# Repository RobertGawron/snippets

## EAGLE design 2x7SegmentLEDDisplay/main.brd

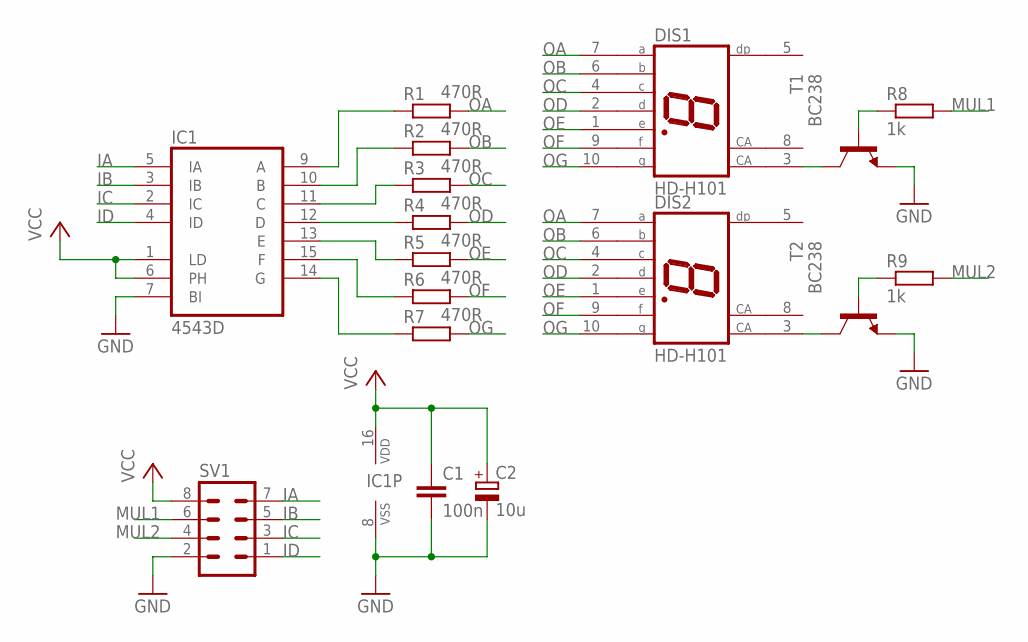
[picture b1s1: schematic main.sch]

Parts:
C1: 100n; C1206
C2: 10u; SMC_A
DIS1, DIS2: HD-H101; HDSP-M
IC1: 4543D; SO16
R1, R2, R3, R4, R5, R6, R7: 470R; R1206
R8, R9: 1k; R1206
SV1: MA04-2
T1, T2: BC238; TO92

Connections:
GND: C1.2, C2.-, IC1.7 (BI), IC1.8 (VSS), SV1.2, T1.1 (E), T2.1 (E)
IA: IC1.5 (IA), SV1.7
IB: IC1.3 (IB), SV1.5
IC: IC1.2 (IC), SV1.3
ID: IC1.4 (ID), SV1.1
MUL1: R8.2, SV1.6
MUL2: R9.2, SV1.4
unnamed: IC1.12 (D), R4.1
unnamed: IC1.11 (C), R3.1
unnamed: IC1.10 (B), R2.1
unnamed: IC1.13 (E), R5.1
unnamed: DIS1.3 (CA), T1.3 (C)
unnamed: R8.1, T1.2 (B)
unnamed: IC1.15 (F), R6.1
unnamed: IC1.9 (A), R1.1
unnamed: IC1.14 (G), R7.1
unnamed: R9.1, T2.2 (B)
unnamed: DIS2.3 (CA), T2.3 (C)
OA: DIS1.7 (A), DIS2.7 (A), R1.2
OB: DIS1.6 (B), DIS2.6 (B), R2.2
OC: DIS1.4 (C), DIS2.4 (C), R3.2
OD: DIS1.2 (D), DIS2.2 (D), R4.2
OE: DIS1.1 (E), DIS2.1 (E), R5.2
OF: DIS1.9 (F), DIS2.9 (F), R6.2
OG: DIS1.10 (G), DIS2.10 (G), R7.2
VCC: C1.1, C2.+, IC1.1 (LD), IC1.6 (PH), IC1.16 (VDD), SV1.8

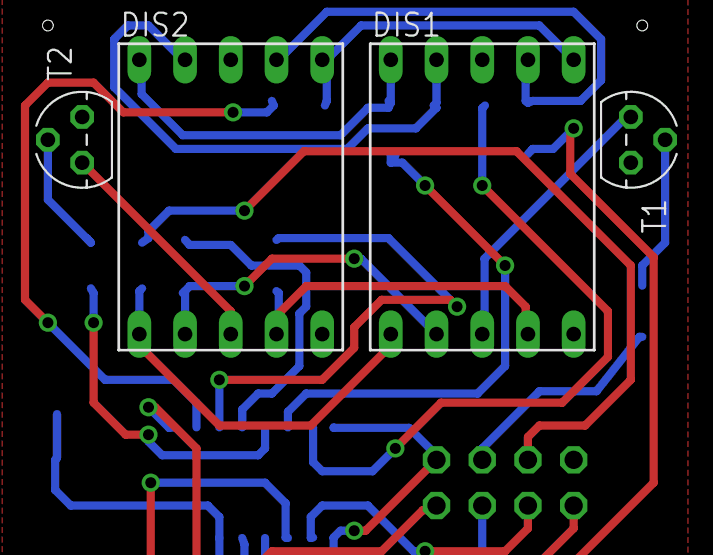
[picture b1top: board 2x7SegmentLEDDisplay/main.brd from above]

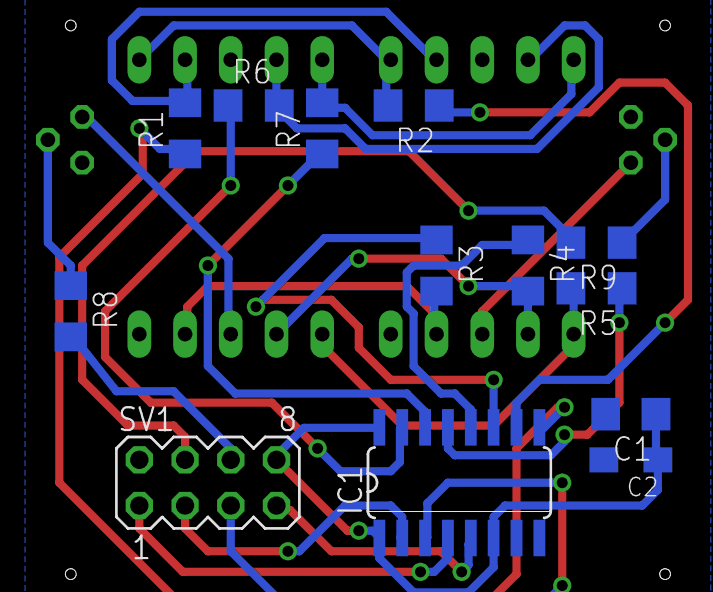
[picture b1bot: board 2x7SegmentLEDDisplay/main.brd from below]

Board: 2 copper layers, 17 parts (13 on the bottom side), 26 nets.

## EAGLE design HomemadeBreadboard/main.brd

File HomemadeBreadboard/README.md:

# Homemade breadboard.

For more info please visit full article:
http://robertgawron.blogspot.com/2015/07/homemade-breadboard.html

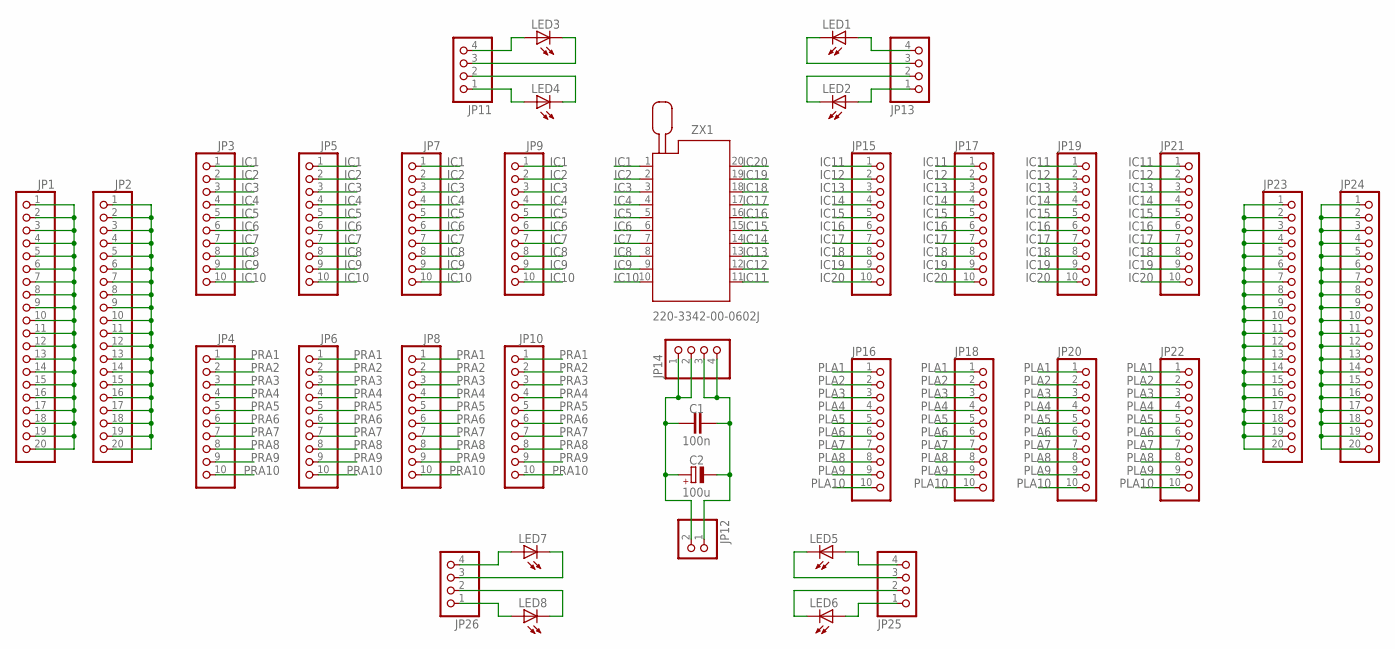
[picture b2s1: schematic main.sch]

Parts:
C1: 100n; C1206
C2: 100u; SMC_A
JP1, JP2, JP23, JP24: PINHD-1X20; 1X20
JP3, JP4, JP5, JP6, JP7, JP8, JP9, JP10, JP15, JP16, JP17, JP18, JP19, JP20, JP21, JP22: PINHD-1X10; 1X10
JP11, JP13, JP14, JP25, JP26: PINHD-1X4; 1X04
JP12: PINHD-1X2/90; 1X02/90
LED1, LED2, LED3, LED4, LED5, LED6, LED7, LED8: LEDSFH482; SFH482
ZX1: 220-3342-00-0602J

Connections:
GND: C1.2, C2.-, JP12.1, JP14.3, JP14.4
IC1: JP3.1, JP5.1, JP7.1, JP9.1, ZX1.1
IC2: JP3.2, JP5.2, JP7.2, JP9.2, ZX1.2
IC3: JP3.3, JP5.3, JP7.3, JP9.3, ZX1.3
IC4: JP3.4, JP5.4, JP7.4, JP9.4, ZX1.4
IC5: JP3.5, JP5.5, JP7.5, JP9.5, ZX1.5
IC6: JP3.6, JP5.6, JP7.6, JP9.6, ZX1.6
IC7: JP3.7, JP5.7, JP7.7, JP9.7, ZX1.7
IC8: JP3.8, JP5.8, JP7.8, JP9.8, ZX1.8
IC9: JP3.9, JP5.9, JP7.9, JP9.9, ZX1.9
IC10: JP3.10, JP5.10, JP7.10, JP9.10, ZX1.10
IC11: JP15.1, JP17.1, JP19.1, JP21.1, ZX1.11
IC12: JP15.2, JP17.2, JP19.2, JP21.2, ZX1.12
IC13: JP15.3, JP17.3, JP19.3, JP21.3, ZX1.13
IC14: JP15.4, JP17.4, JP19.4, JP21.4, ZX1.14
IC15: JP15.5, JP17.5, JP19.5, JP21.5, ZX1.15
IC16: JP15.6, JP17.6, JP19.6, JP21.6, ZX1.16
IC17: JP15.7, JP17.7, JP19.7, JP21.7, ZX1.17
IC18: JP15.8, JP17.8, JP19.8, JP21.8, ZX1.18
IC19: JP15.9, JP17.9, JP19.9, JP21.9, ZX1.19
IC20: JP15.10, JP17.10, JP19.10, JP21.10, ZX1.20
unnamed: JP1.1, JP1.2, JP1.3, JP1.4, JP1.5, JP1.6, JP1.7, JP1.8, JP1.9, JP1.10, JP1.11, JP1.12, JP1.13, JP1.14, JP1.15, JP1.16, JP1.17, JP1.18, JP1.19, JP1.20
unnamed: JP2.1, JP2.2, JP2.3, JP2.4, JP2.5, JP2.6, JP2.7, JP2.8, JP2.9, JP2.10, JP2.11, JP2.12, JP2.13, JP2.14, JP2.15, JP2.16, JP2.17, JP2.18, JP2.19, JP2.20
unnamed: JP24.1, JP24.2, JP24.3, JP24.4, JP24.5, JP24.6, JP24.7, JP24.8, JP24.9, JP24.10, JP24.11, JP24.12, JP24.13, JP24.14, JP24.15, JP24.16, JP24.17, JP24.18, JP24.19, JP24.20
unnamed: JP23.1, JP23.2, JP23.3, JP23.4, JP23.5, JP23.6, JP23.7, JP23.8, JP23.9, JP23.10, JP23.11, JP23.12, JP23.13, JP23.14, JP23.15, JP23.16, JP23.17, JP23.18, JP23.19, JP23.20
unnamed: JP13.3, LED1.K (C)
unnamed: JP13.4, LED1.A
unnamed: JP13.2, LED2.K (C)
unnamed: JP13.1, LED2.A
unnamed: JP11.3, LED3.K (C)
unnamed: JP11.4, LED3.A
unnamed: JP11.2, LED4.K (C)
unnamed: JP11.1, LED4.A
unnamed: JP25.3, LED5.K (C)
unnamed: JP25.4, LED5.A
unnamed: JP25.2, LED6.K (C)
unnamed: JP25.1, LED6.A
unnamed: JP26.3, LED7.K (C)
unnamed: JP26.4, LED7.A
unnamed: JP26.2, LED8.K (C)
unnamed: JP26.1, LED8.A
PLA1: JP16.1, JP18.1, JP20.1, JP22.1
PLA2: JP16.2, JP18.2, JP20.2, JP22.2
PLA3: JP16.3, JP18.3, JP20.3, JP22.3
PLA4: JP16.4, JP18.4, JP20.4, JP22.4
PLA5: JP16.5, JP18.5, JP20.5, JP22.5
PLA6: JP16.6, JP18.6, JP20.6, JP22.6
PLA7: JP16.7, JP18.7, JP20.7, JP22.7
PLA8: JP16.8, JP18.8, JP20.8, JP22.8
PLA9: JP16.9, JP18.9, JP20.9, JP22.9
PLA10: JP16.10, JP18.10, JP20.10, JP22.10
PRA1: JP4.1, JP6.1, JP8.1, JP10.1
PRA2: JP4.2, JP6.2, JP8.2, JP10.2
PRA3: JP4.3, JP6.3, JP8.3, JP10.3
PRA4: JP4.4, JP6.4, JP8.4, JP10.4
PRA5: JP4.5, JP6.5, JP8.5, JP10.5
PRA6: JP4.6, JP6.6, JP8.6, JP10.6
PRA7: JP4.7, JP6.7, JP8.7, JP10.7
PRA8: JP4.8, JP6.8, JP8.8, JP10.8
PRA9: JP4.9, JP6.9, JP8.9, JP10.9
PRA10: JP4.10, JP6.10, JP8.10, JP10.10
VCC: C1.1, C2.+, JP12.2, JP14.1, JP14.2

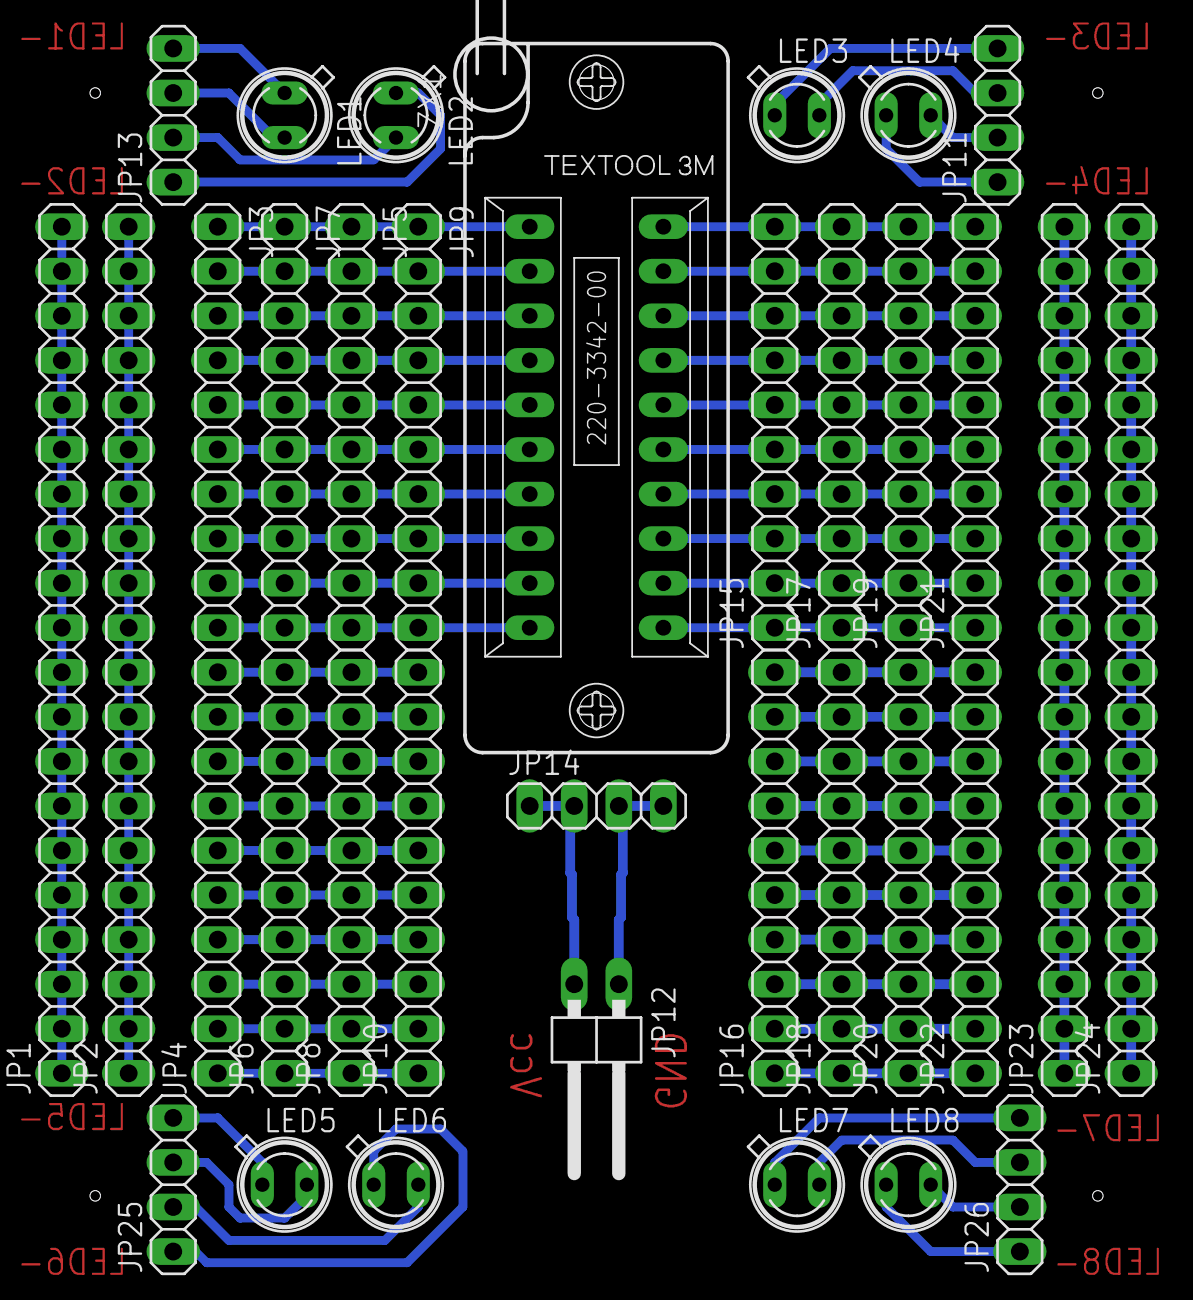
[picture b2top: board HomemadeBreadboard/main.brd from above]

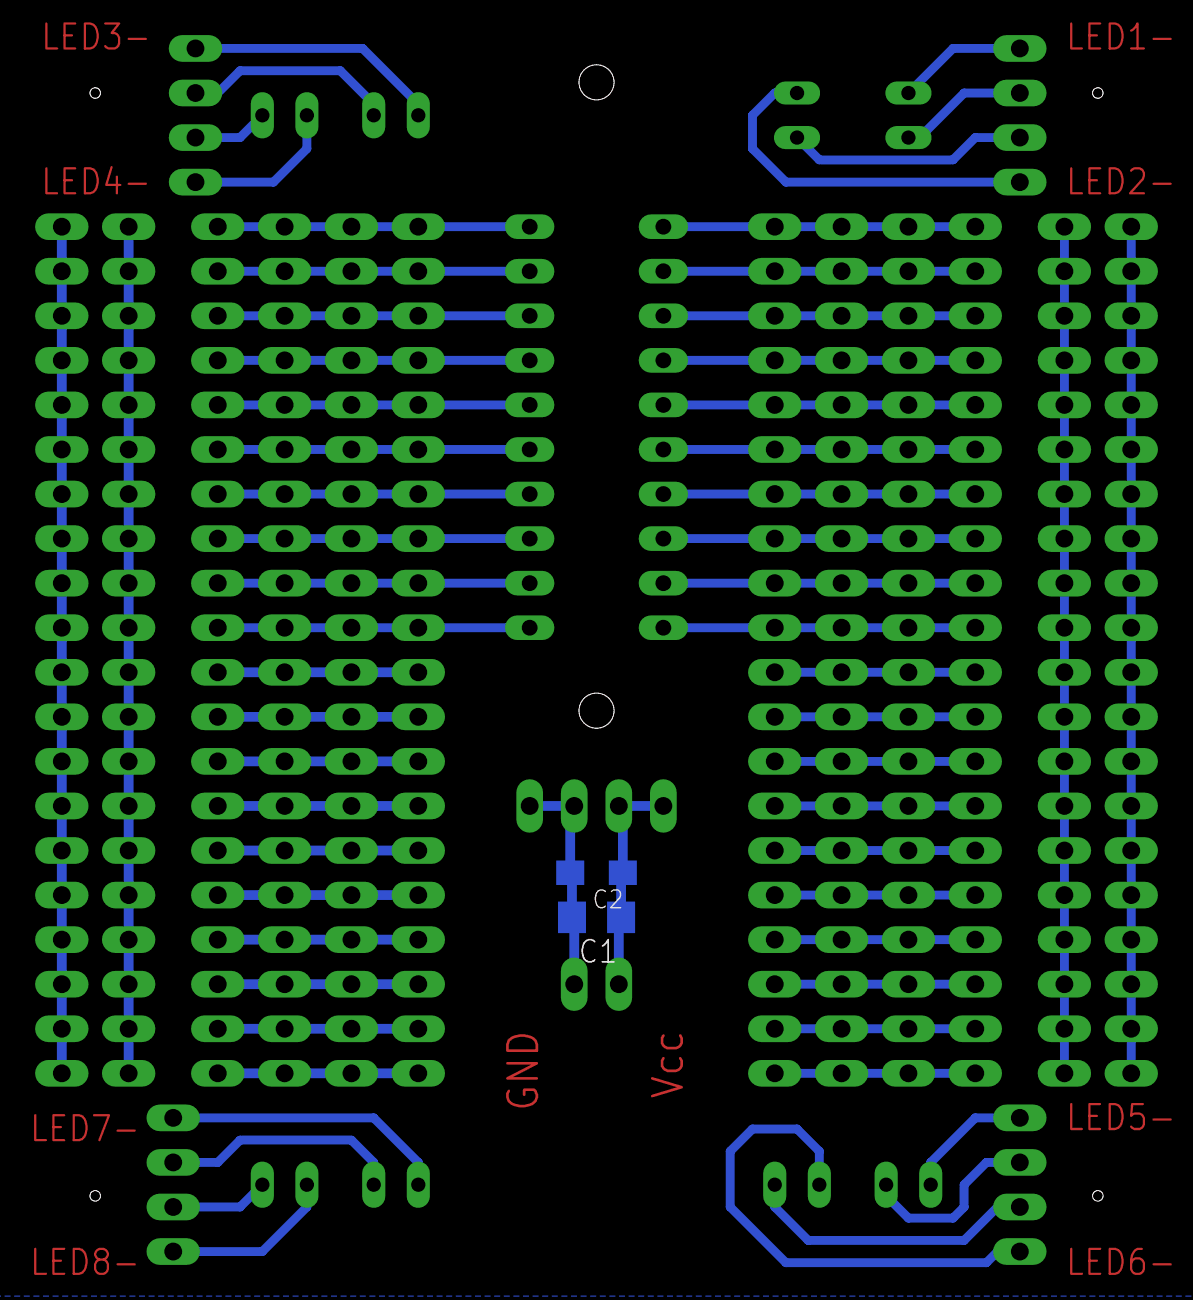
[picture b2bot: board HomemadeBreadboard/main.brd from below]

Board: 2 copper layers, 37 parts (2 on the bottom side), 62 nets.

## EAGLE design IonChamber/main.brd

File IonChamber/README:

This project is not working. It's unfinished.

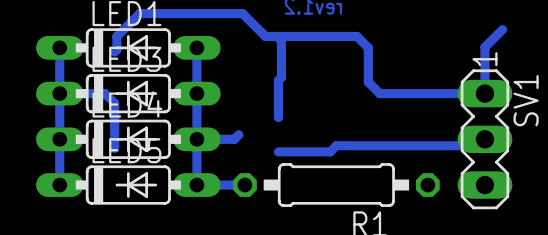
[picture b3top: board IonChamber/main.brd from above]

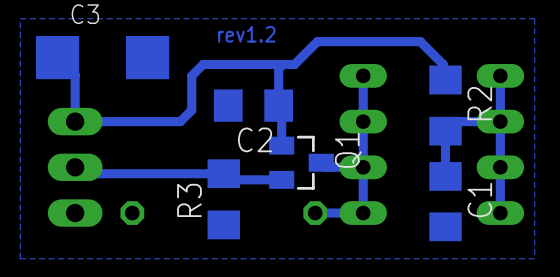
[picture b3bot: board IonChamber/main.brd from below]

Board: 2 copper layers, 12 parts (6 on the bottom side), 5 nets.

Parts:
C1, C2: 100n; C1206
C3: 100u; SMC_C
LED1, LED3, LED4, LED5: 1N4148; DO35-7
Q1: J111; SOT23
R1: 10M; 0207/10
R2: 1k; R1206
R3: 100k; R1206
SV1: connector; MA03-1

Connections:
GND: C1.2, C2.2, C3.-, R1.1, R3.1, SV1.3
unnamed: C1.1, LED1.C, LED3.C, LED4.C, LED5.C, R2.2
unnamed: Q1.2, R3.2, SV1.2
unnamed: LED1.A, LED3.A, LED4.A, LED5.A, Q1.3, R1.2
unnamed: C2.1, C3.+, Q1.1, R2.1, SV1.1

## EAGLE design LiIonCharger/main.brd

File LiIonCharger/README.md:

# USB powered Li-Ion charger.

Be careful, incorrectly connected or overcharged Li-Ion battery can explode or burn. Always load them when you are around.

For more info please visit full article:
http://robertgawron.blogspot.com/2015/07/how-to-make-usb-li-ion-charger.html

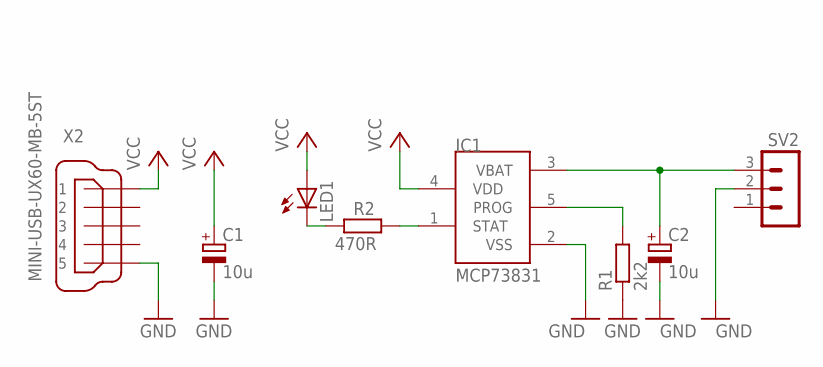
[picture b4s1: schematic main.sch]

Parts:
C1, C2: 10u; SMC_A
IC1: MCP73831; SOT23-5L
LED1: LEDSML0805; SML0805
R1: 2k2; R1206
R2: 470R; R1206
SV2: MA03-1
X2: MINI-USB-UX60-MB-5ST; UX60-MB-5ST

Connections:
GND: C1.-, C2.-, IC1.2 (VSS), R1.1, SV2.2, X2.5
unnamed: IC1.5 (PROG), R1.2
unnamed: LED1.C, R2.1
unnamed: IC1.1 (STAT), R2.2
unnamed: C2.+, IC1.3 (VBAT), SV2.3
VCC: C1.+, IC1.4 (VDD), LED1.A, X2.1

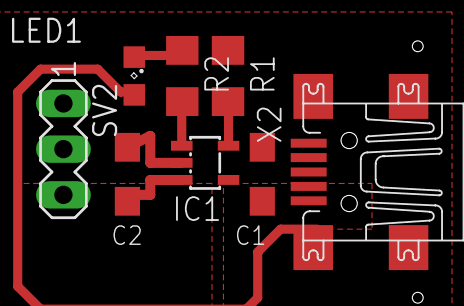
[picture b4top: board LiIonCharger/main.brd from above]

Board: 2 copper layers, 8 parts (0 on the bottom side), 6 nets.

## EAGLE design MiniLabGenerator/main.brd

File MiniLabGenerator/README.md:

# Square wave generator.

For more info please visit full article:
http://robertgawron.blogspot.com/2015/06/poor-mans-lab-generator.html

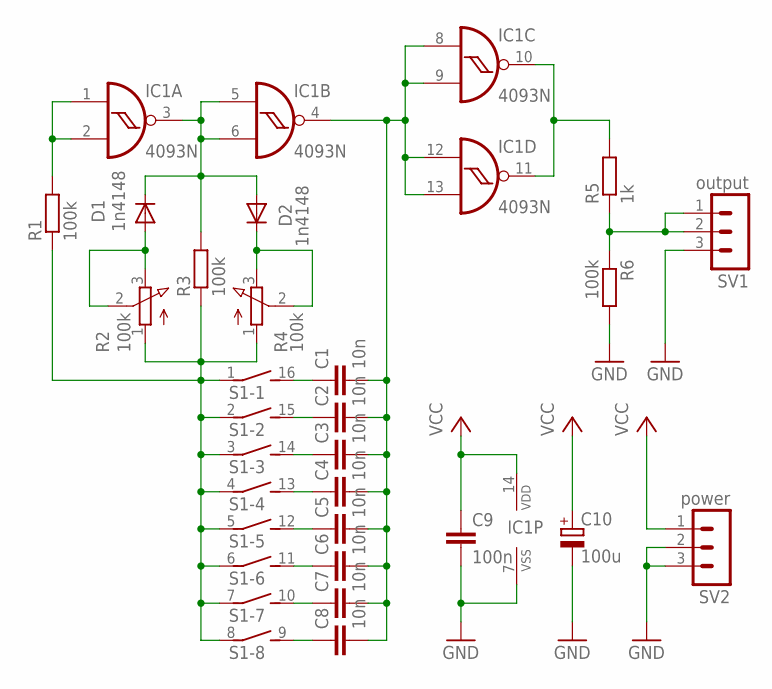
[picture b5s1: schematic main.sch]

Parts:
C1, C2, C3, C4, C5, C6, C7, C8: 10n; C050-025X075
C9: 100n; C1206
C10: 100u; E2,5-7
D1, D2: 1n4148; MINIMELF
IC1: 4093N; DIL14
R1, R3, R6: 100k; 0204V
R2, R4: 100k; 3RP/1610N
R5: 1k; 0204V
S1: DIP08S
SV1: output; MA03-1
SV2: power; MA03-1

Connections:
GND: C9.2, C10.-, IC1.7 (VSS), R6.2, SV1.3, SV2.2, SV2.3
unnamed: D1.C, D2.A, IC1.3 (O), IC1.5 (I0), IC1.6 (I1), R3.2
unnamed: IC1.1 (I0), IC1.2 (I1), R1.2
unnamed: D1.A, R2.2 (S), R2.3 (E)
unnamed: C1.1, S1.16 (2)
unnamed: IC1.10 (O), IC1.11 (O), R5.2
unnamed: R5.1, R6.1, SV1.1, SV1.2
unnamed: C2.1, S1.15 (2)
unnamed: C3.1, S1.14 (2)
unnamed: C4.1, S1.13 (2)
unnamed: C5.1, S1.12 (2)
unnamed: C6.1, S1.11 (2)
unnamed: C7.1, S1.10 (2)
unnamed: C8.1, S1.9 (2)
unnamed: C1.2, C2.2, C3.2, C4.2, C5.2, C6.2, C7.2, C8.2, IC1.4 (O), IC1.8 (I0), IC1.9 (I1), IC1.12 (I0), IC1.13 (I1)
unnamed: D2.C, R4.2 (S), R4.3 (E)
unnamed: R1.1, R2.1 (A), R3.1, R4.1 (A), S1.1, S1.2 (1), S1.3 (1), S1.4 (1), S1.5 (1), S1.6 (1), S1.7 (1), S1.8 (1)
VCC: C9.1, C10.+, IC1.14 (VDD), SV2.1

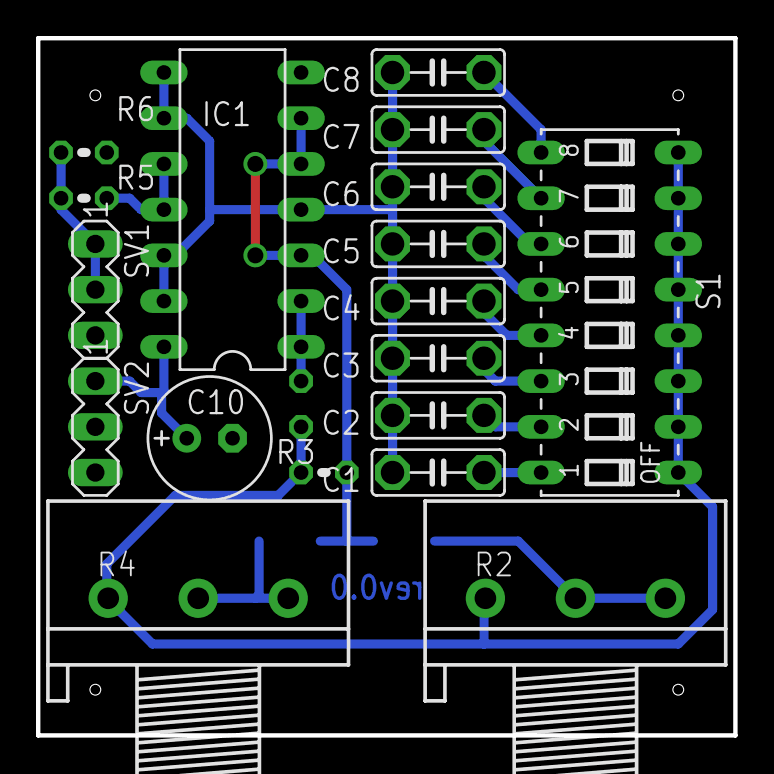
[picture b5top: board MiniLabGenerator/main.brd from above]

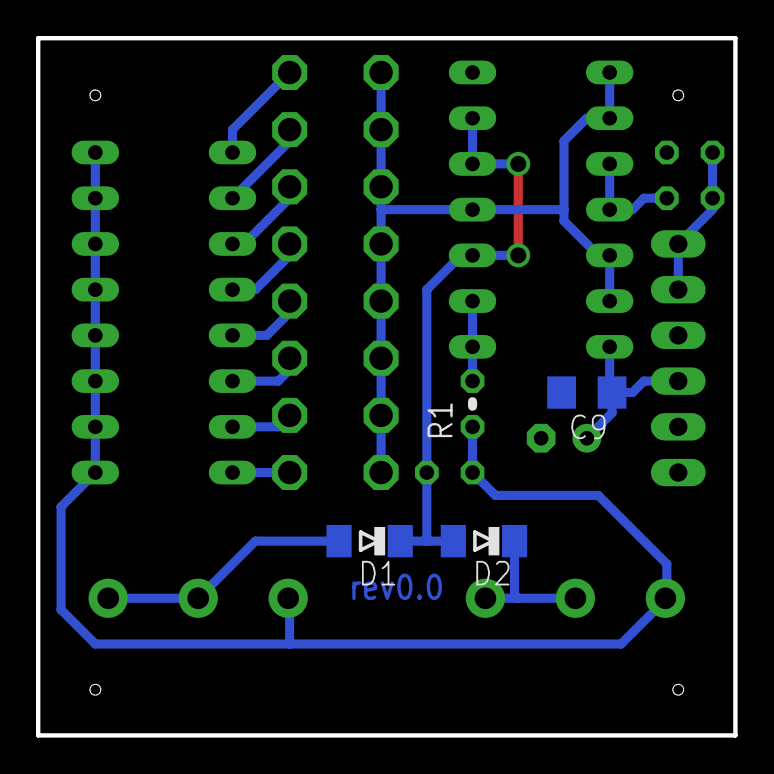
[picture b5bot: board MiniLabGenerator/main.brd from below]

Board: 2 copper layers, 38.7 x 38.7 mm, 22 parts (4 on the bottom side), 18 nets.

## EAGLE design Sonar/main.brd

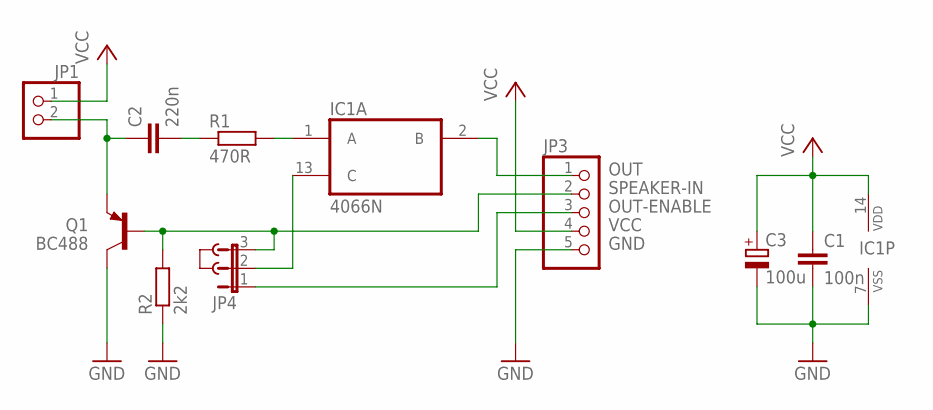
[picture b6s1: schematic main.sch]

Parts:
C1: 100n; C1206
C2: 220n; C025-025X050
C3: 100u; E2-5
IC1: 4066N; DIL14
J1: JUMPER; JUMP
JP1: PINHD-1X2; 1X02
JP3: PINHD-1X5; 1X05
JP4: JP2E; JP2
Q1: BC488; TO92-EBC
R1: 470R; 0204/7
R2: 2k2; R1206

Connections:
GND: C1.2, C3.-, IC1.7 (VSS), JP3.5, Q1.C, R2.1
unnamed: C2.1, JP1.2, Q1.E
unnamed: C2.2, R1.1
unnamed: IC1.1 (A), R1.2
unnamed: IC1.13 (C), JP4.2
OUT: IC1.2 (B), JP3.1
OUT-ENABLE: JP3.3, JP4.1
SPEAKER-IN: JP3.2, JP4.3, Q1.B, R2.2
VCC: C1.1, C3.+, IC1.14 (VDD), JP1.1, JP3.4

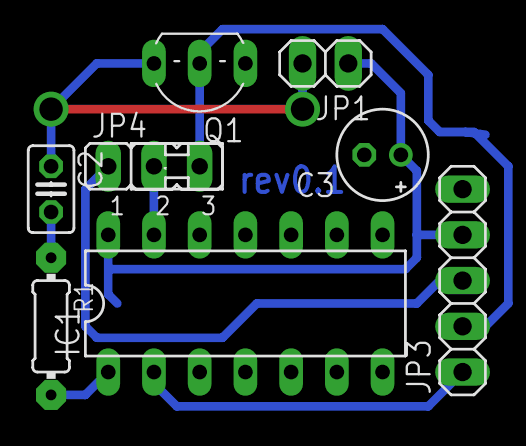
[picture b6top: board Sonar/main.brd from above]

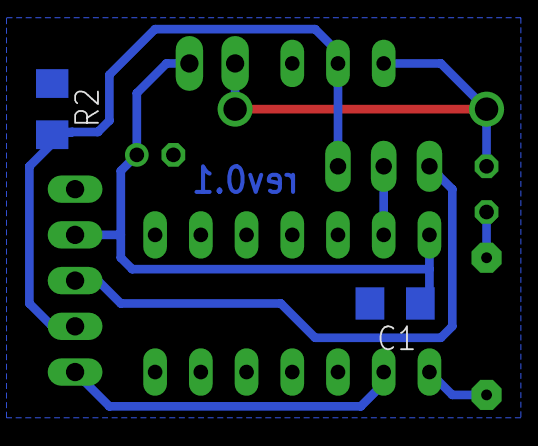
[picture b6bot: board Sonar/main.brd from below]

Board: 2 copper layers, 11 parts (2 on the bottom side), 9 nets.

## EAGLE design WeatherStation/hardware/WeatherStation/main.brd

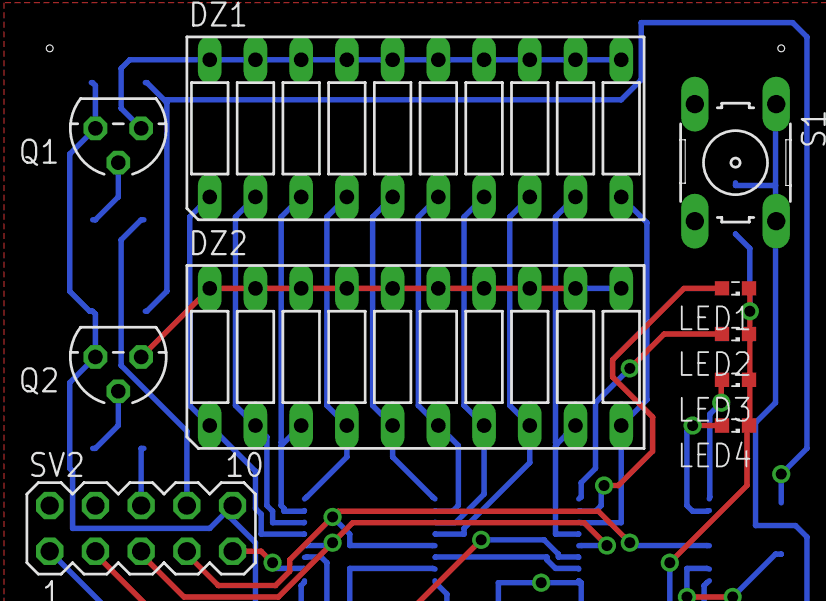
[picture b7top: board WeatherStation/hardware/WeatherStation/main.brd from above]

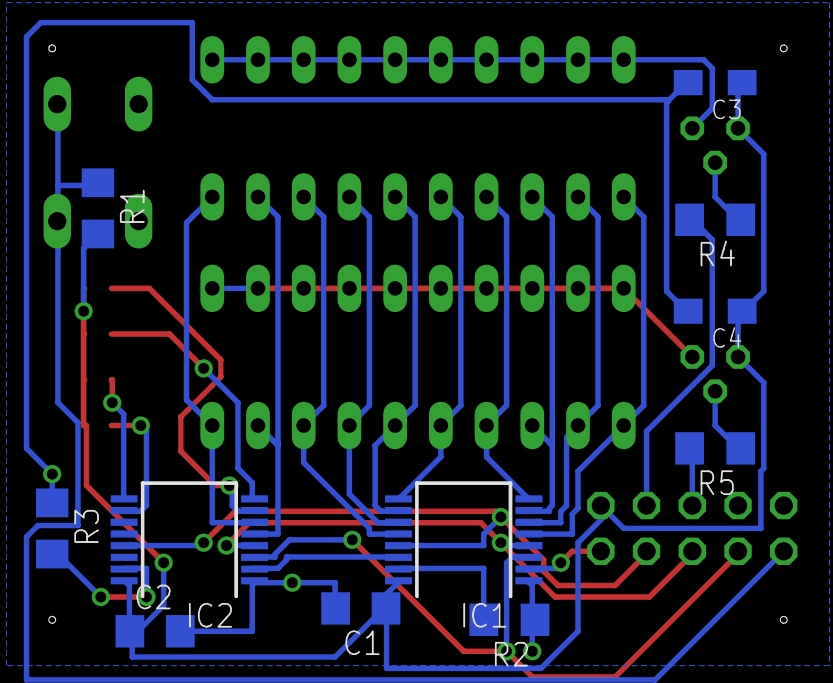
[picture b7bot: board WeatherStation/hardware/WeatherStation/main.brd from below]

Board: 2 copper layers, 21 parts (11 on the bottom side), 30 nets.

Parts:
C1, C2: 100n; C1206
C3, C4: 1u; SMC_A
DZ1, DZ2: LB10
IC1, IC2: SCT2167CSSG; SSOP16
LED1, LED2, LED3, LED4: SML0603
Q1, Q2: BC327; TO92
R1, R2, R3, R4, R5: 1k; R1206
S1: B3F-10XX
SV2: MA05-2

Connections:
CU-CLK: IC1.3, IC2.3, SV2.3
CU-CTRL: R1.1, S1.1, S1.2, SV2.1
CU-LA: IC1.4, IC2.4, SV2.5
CU-OE: IC1.13, IC2.13, SV2.7
CU-SDI: IC1.2, SV2.9
GND: C1.2, C2.2, C3.-, C4.-, IC1.1, IC2.1, R2.1, R3.1, S1.3, S1.4, SV2.2
LED1: DZ1.1, DZ2.1, IC1.5
LED2: DZ1.2, DZ2.2, IC1.6
LED3: DZ1.3, DZ2.3, IC1.7
LED4: DZ1.4, DZ2.4, IC1.8
LED5: DZ1.5, DZ2.5, IC1.9
LED6: DZ1.6, DZ2.6, IC1.10
LED7: DZ1.7, DZ2.7, IC1.11
LED8: DZ1.8, DZ2.8, IC1.12
LED9: DZ1.9, DZ2.9, IC2.5
LED10: DZ1.10, DZ2.10, IC2.6
LED11: IC2.7, LED1.A
LED12: IC2.8, LED2.A
LED13: IC2.9, LED3.A
LED14: IC2.10, LED4.A
MUL1: R4.2, SV2.8
MUL2: R5.2, SV2.6
unnamed: DZ1.11, DZ1.12, DZ1.13, DZ1.14, DZ1.15, DZ1.16, DZ1.17, DZ1.18, DZ1.19, DZ1.20, Q1.3
unnamed: IC1.14, IC2.2
unnamed: Q1.2, R4.1
unnamed: DZ2.11, DZ2.12, DZ2.13, DZ2.14, DZ2.15, DZ2.16, DZ2.17, DZ2.18, DZ2.19, DZ2.20, Q2.3
unnamed: Q2.2, R5.1
unnamed: IC1.15, R2.2
unnamed: IC2.15, R3.2
VCC: C1.1, C2.1, C3.+, C4.+, IC1.16, IC2.16, LED1.C, LED2.C, LED3.C, LED4.C, Q1.1, Q2.1, R1.2, SV2.10

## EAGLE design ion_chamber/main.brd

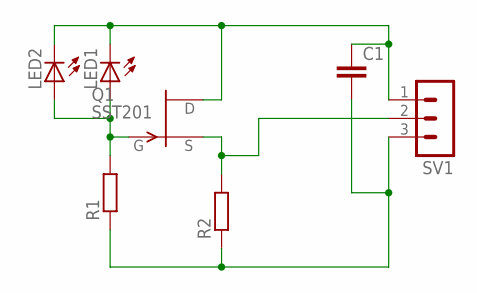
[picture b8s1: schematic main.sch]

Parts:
C1: C-EU025-050X050; C025-050X050
LED1, LED2: LEDSFH480; SFH480
Q1: SST201; SOT23
R1, R2: R-EU_0204/7; 0204/7
SV1: MA03-1

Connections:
unnamed: Q1.2 (S), R2.2, SV1.2
unnamed: C1.2, R1.1, R2.1, SV1.3
unnamed: LED1.A, LED2.A, Q1.3 (G), R1.2
unnamed: C1.1, LED1.K (C), LED2.K (C), Q1.1 (D), SV1.1

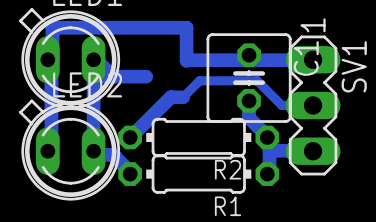
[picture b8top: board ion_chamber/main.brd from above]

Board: 2 copper layers, 7 parts (1 on the bottom side), 4 nets.
